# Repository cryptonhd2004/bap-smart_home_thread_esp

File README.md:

# Prvky chytré domácnosti s ESP32 používající protokol Thread

*Smart home components based on ESP32 using the Thread protocol*

Bakalářská práce, VUT v Brně, FEKT, Ústav telekomunikací, 2026/2027.

- **Autor:** David Šindelář
- **Vedoucí:** doc. Ing. Ivo Lattenberg, Ph.D.
- **Detail práce:** https://www.vut.cz/studenti/zav-prace/detail/179908

## Výkresy DPS a schémata

| Zařízení | Schéma zapojení | Osazovací výkres DPS | Další |
|---|---|---|---|
| Čidlo teploty | [PDF](https://github.com/cryptonhd2004/bap-smart_home_thread_esp/blob/main/esp_thread/schema_zapojeni.pdf) | [PDF](https://github.com/cryptonhd2004/bap-smart_home_thread_esp/blob/main/esp_thread/plots/esp_thread__Assembly.pdf) | [projekt KiCad](https://github.com/cryptonhd2004/bap-smart_home_thread_esp/tree/main/esp_thread) |
| Chytré světlo | [PDF](https://github.com/cryptonhd2004/bap-smart_home_thread_esp/blob/main/chytre_svetlo/schema_zapojeni.pdf) | [PDF](https://github.com/cryptonhd2004/bap-smart_home_thread_esp/blob/main/chytre_svetlo/plots/chytre_svetlo__Assembly.pdf) | [projekt KiCad](https://github.com/cryptonhd2004/bap-smart_home_thread_esp/tree/main/chytre_svetlo) |
| Bateriový vypínač | [PDF](https://github.com/cryptonhd2004/bap-smart_home_thread_esp/blob/main/Chytre_Tlacitko_BMS/schema_zapojeni.pdf) | [PDF](https://github.com/cryptonhd2004/bap-smart_home_thread_esp/blob/main/Chytre_Tlacitko_BMS/plots/Chytre_Tlacitko_BMS__Assembly.pdf) | [projekt KiCad](https://github.com/cryptonhd2004/bap-smart_home_thread_esp/tree/main/Chytre_Tlacitko_BMS) |

## O projektu

Návrh a realizace tří zařízení chytré domácnosti, která komunikují protokolem
Matter přes síť Thread (IEEE 802.15.4) a jsou integrována do Home Assistant:

| Zařízení | Napájení | Poznámka |
|---|---|---|
| Čidlo teploty | ze sítě | měření teploty, výběr čidla na základě porovnání |
| Chytré světlo | ze sítě | Router v síti Thread, RGB LED WS2812B (Matter light endpoint) |
| Bateriový vypínač | baterie | ošetření zákmitů, nízká spotřeba |

Všechna zařízení jsou postavena na čipu Espressif ESP32-C6
(modul Seeed Studio XIAO ESP32-C6).

## Struktura repozitáře

| Složka / soubor | Obsah |
|---|---|
| `bap_text/` | text práce (LaTeX, šablona VUT) |
| `chytre_svetlo/` | KiCad: chytré světlo (schéma, DPS, PDF schématu a osazení) |
| `Chytre_Tlacitko_BMS/` | KiCad: bateriový vypínač (schéma, DPS, PDF, iBOM) |
| `esp_thread/` | KiCad: chytrý teploměr (schéma, DPS, PDF, výrobní soubory v `production/`) |
| `test_builds/` | testovací firmware: `c6-matter-teplomer-firmware.factory.bin`, konfigurace `test-teplomer.yaml` a `tlacitko-thread.yaml` |
| `logs_for_debuging/` | logy z ladění, data a skripty porovnání čidel (`output/` – grafy) |
| `github_qr.*` | QR kód repozitáře pro osazení na DPS |

## Stav

| Část | Stav |
|---|---|
| Teoretický úvod (IEEE 802.15.4, CSA) | hotovo |
| Porovnání čidel teploty a vlhkosti | hotovo |
| Schéma a DPS – teploměr, světlo, vypínač | hotovo, připraveno k odsouhlasení |
| Firmware | testovací buildy (teploměr, tlačítko), RGB světlo rozpracováno |
| Text práce | rozpracováno (výsledky, návrh schémat) |

### Porovnání čidel

Referenční čidlo je SHT40 (jen klidné minuty). Rozdíl je počítán jako čidlo minus SHT40.

**Teplota** (n = 3292)

| Čidlo | střední rozdíl [°C] | s_d [°C] | RMSE [°C] | podíl \|d\| ≤ 0,7 °C |
|---|---|---|---|---|
| ALPSTUGA (SEN63C) | 0,19 | 0,18 | 0,26 | 100,0 % |
| BMP180 | −0,74 | 0,02 | 0,74 | 8,3 % |
| DHT11 | 0,00 | 0,04 | 0,04 | 100,0 % |
| TIMMERFLOTTE | −0,52 | 0,07 | 0,53 | 99,4 % |

**Vlhkost** (n = 2882)

| Čidlo | střední rozdíl [%RH] | s_d [%RH] | RMSE [%RH] | podíl \|d\| ≤ 3,0 %RH |
|---|---|---|---|---|
| ALPSTUGA (SEN63C) | −8,86 | 0,69 | 8,89 | 0,0 % |
| DHT11 | −1,70 | 0,94 | 1,94 | 99,9 % |
| TIMMERFLOTTE | −6,21 | 0,87 | 6,27 | 0,0 % |

## Sestavení textu

Hlavní soubor je `bap_text/sablona-prace.tex`. Překlad: pdfLaTeX dvakrát.
Seznam literatury je psán ručně v `bap_text/text/literatura.tex`.

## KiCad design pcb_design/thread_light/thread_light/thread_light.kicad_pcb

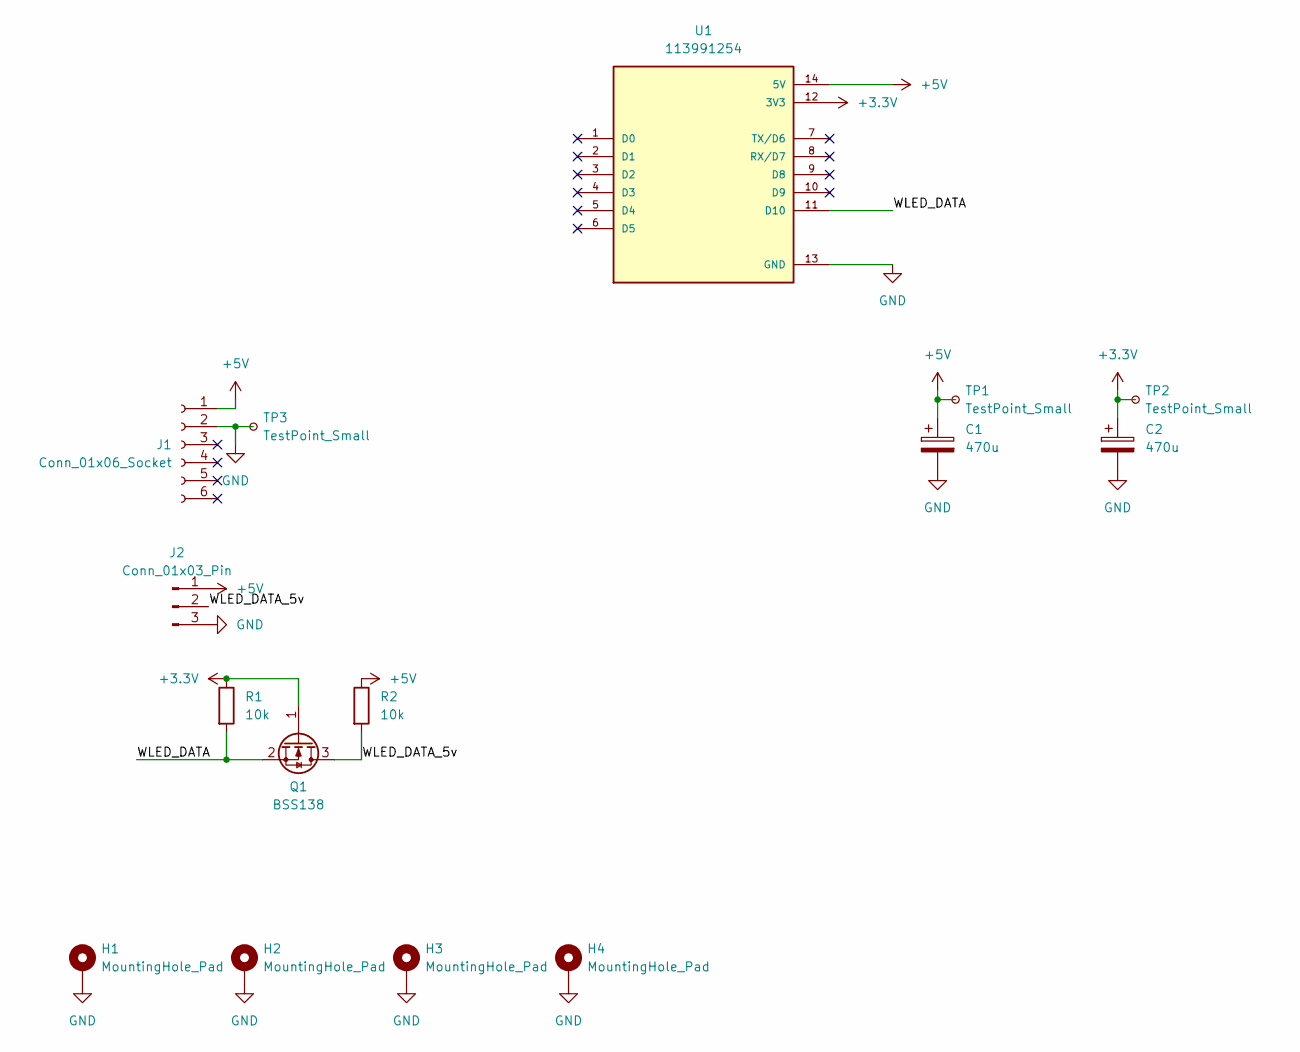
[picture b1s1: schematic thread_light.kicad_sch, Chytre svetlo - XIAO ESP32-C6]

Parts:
C1, C2: 470u; CP_Radial_D12.5mm_P5.00mm
H1, H2, H3, H4: MountingHole_Pad; MountingHole_3.2mm_M3_ISO14580_Pad_TopBottom
J1: Conn_01x06_Socket; PinSocket_1x06_P2.54mm_Vertical
J2: Conn_01x03_Pin; PinSocket_1x03_P2.54mm_Vertical
Q1: BSS138; SOT-23
R1, R2: 10k; R_0805_2012Metric
TP1, TP2, TP3: TestPoint_Small; TestPoint_Pad_D1.5mm
U1: 113991254; MODULE_113991254; PARTREV v1.0

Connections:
+3.3V: C2.1, Q1.1 (G), R1.1, TP2.1 (1_1), U1.12 (3V3)
+5V: C1.1, J1.1, J2.1, R2.1, TP1.1 (1_1), U1.14 (5V)
/WLED_DATA: Q1.2 (S), R1.2, U1.11 (D10)
/WLED_DATA_5v: J2.2, Q1.3 (D), R2.2
GND: C1.2, C2.2, H1.1 (1_1), H2.1 (1_1), H3.1 (1_1), H4.1 (1_1), J1.2, J2.3, TP3.1 (1_1), U1.13 (GND)

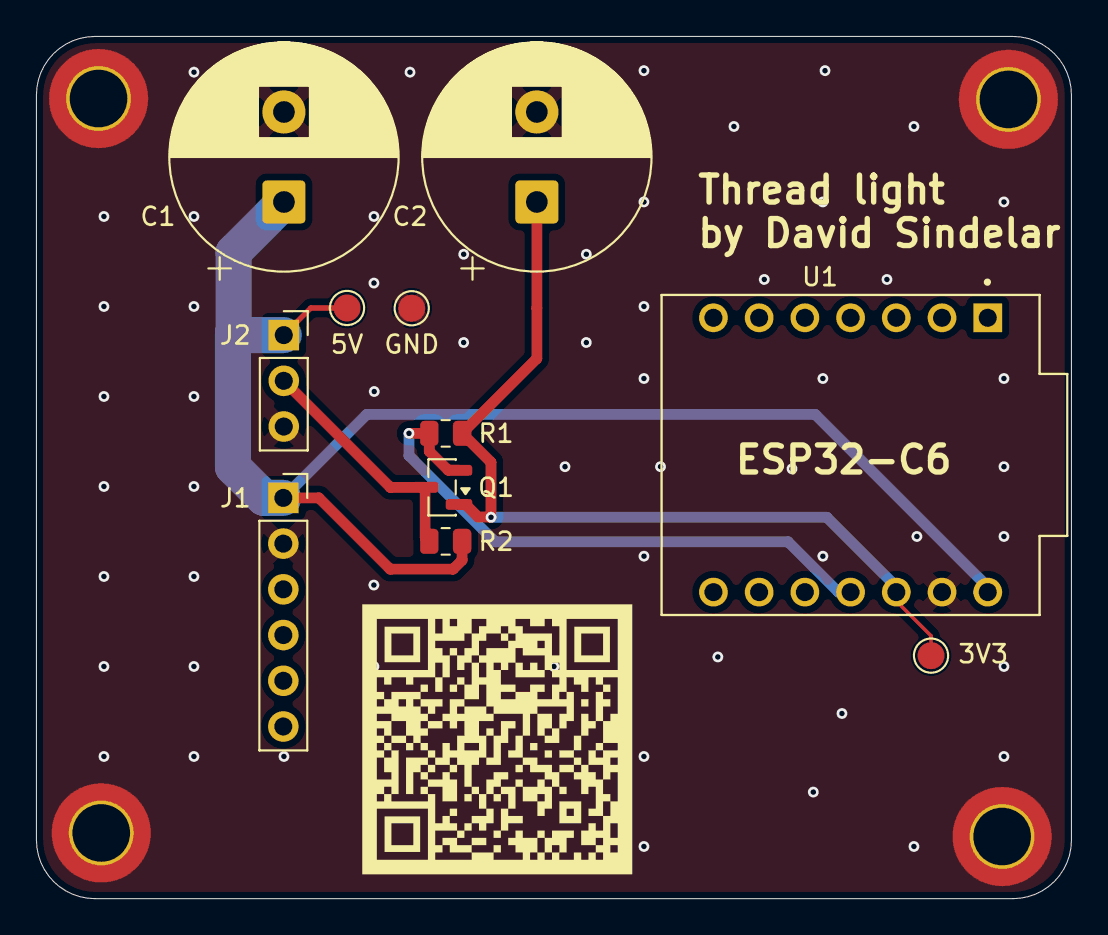
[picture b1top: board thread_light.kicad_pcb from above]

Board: 2 copper layers, 57.5 x 47.9 mm, 15 parts (0 on the bottom side), 5 nets.

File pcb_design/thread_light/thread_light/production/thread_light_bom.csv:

Designator,Footprint,Quantity,Value,LCSC Part #
"C1, C2",CP_Radial_D12.5mm_P5.00mm,2,470u,
J1,PinSocket_1x06_P2.54mm_Vertical,1,Conn_01x06_Socket,
J2,PinSocket_1x03_P2.54mm_Vertical,1,Conn_01x03_Pin,
Q1,SOT-23,1,BSS138,
"R1, R2",0805,2,10k,
"TP1, TP2, TP3",TestPoint_Pad_D1.5mm,3,TestPoint_Small,
U1,MODULE_113991254,1,113991254,

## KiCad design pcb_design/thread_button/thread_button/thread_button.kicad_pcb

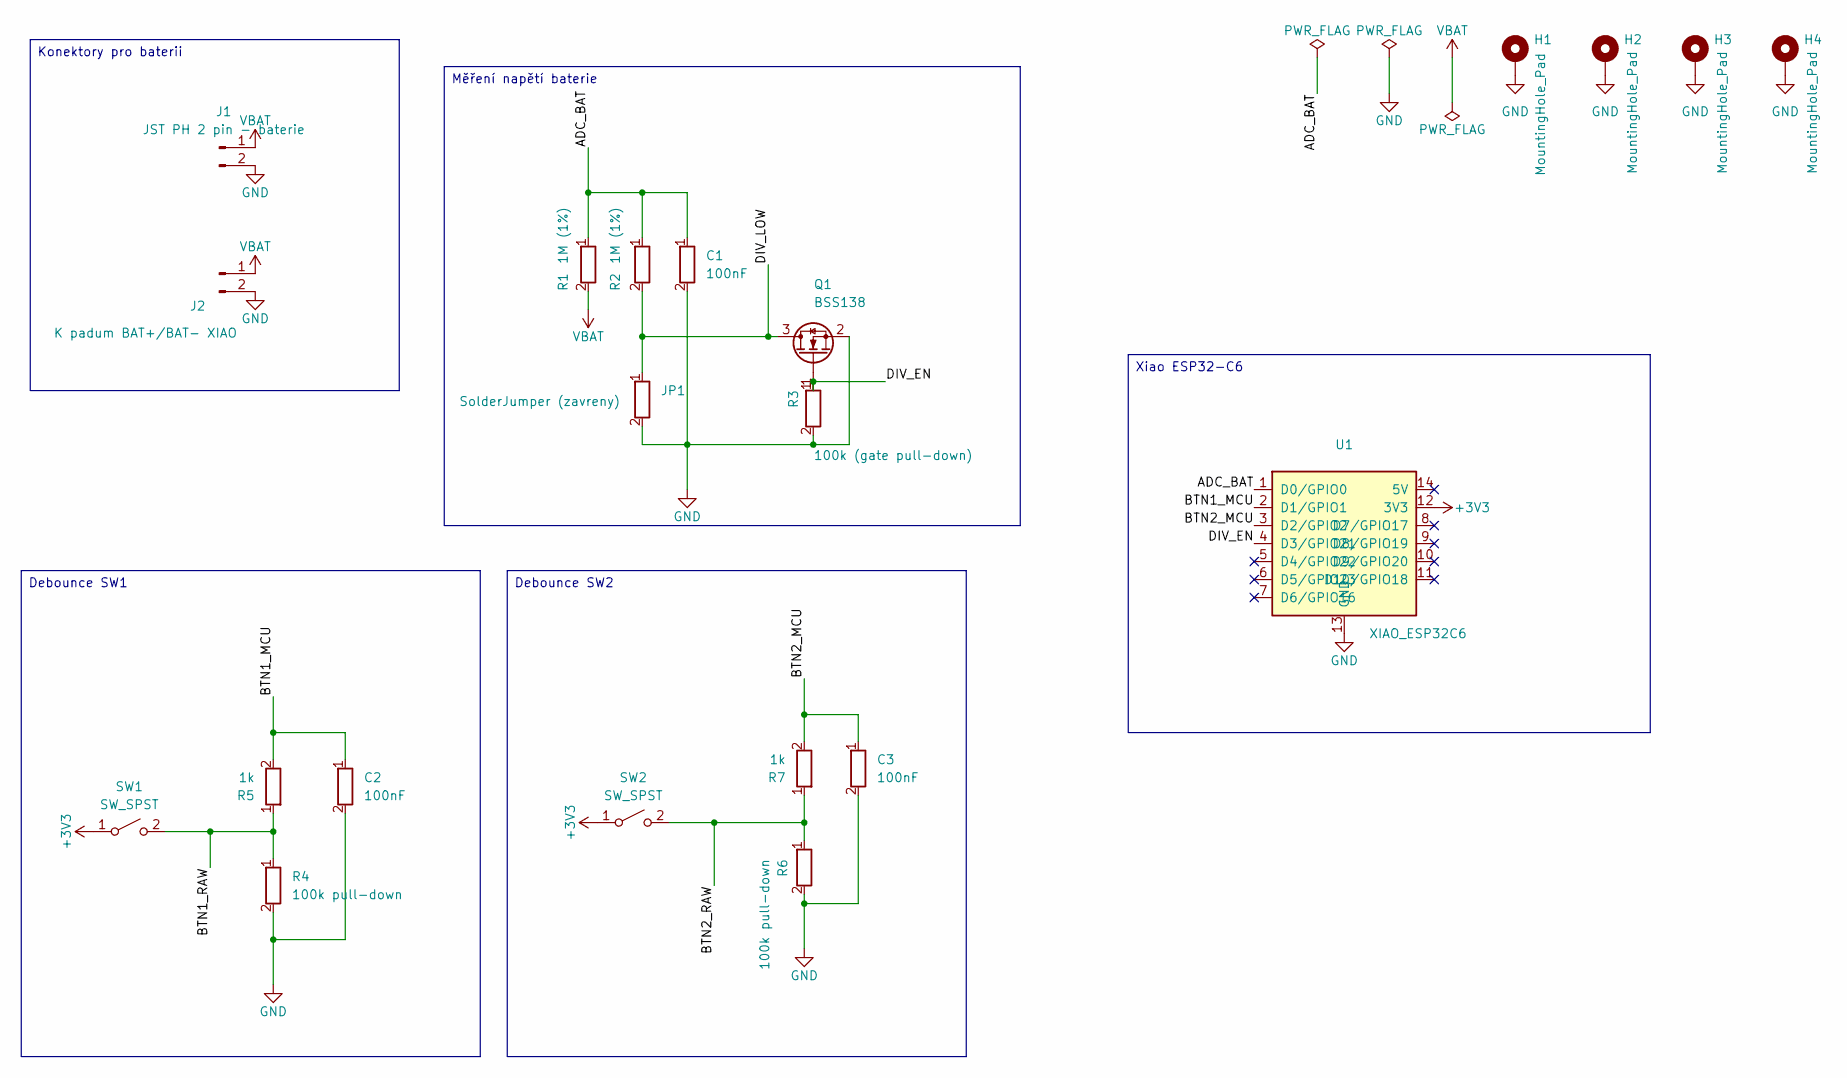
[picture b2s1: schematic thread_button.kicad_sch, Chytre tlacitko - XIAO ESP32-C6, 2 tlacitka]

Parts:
C1, C2, C3: 100nF; C_0805_2012Metric
H1, H2, H3, H4: MountingHole_Pad; MountingHole_2.5mm_Pad
J1: JST PH 2 pin - baterie; JST_PH_B2B-PH-K_1x02_P2.00mm_Vertical
J2: K padum BAT+/BAT- XIAO; JST_PH_B2B-PH-K_1x02_P2.00mm_Vertical
JP1: SolderJumper (zavreny); SolderJumper-2_P1.3mm_Bridged_RoundedPad1.0x1.5mm
Q1: BSS138; SOT-23
R1, R2: 1M (1%); R_0805_2012Metric
R3: 100k (gate pull-down); R_0805_2012Metric
R4, R6: 100k pull-down; R_0805_2012Metric
R5, R7: 1k; R_0805_2012Metric
SW1, SW2: SW_SPST; SW_PUSH-12mm_Wuerth-430476085716
U1: XIAO_ESP32C6; MODULE_113991254

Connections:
+3V3: SW1.1 (A), SW2.1 (A), U1.12 (3V3)
/ADC_BAT: C1.1, R1.1, R2.1, U1.1 (D0/GPIO0)
/BTN1_MCU: C2.1, R5.2, U1.2 (D1/GPIO1)
/BTN1_RAW: R4.1, R5.1, SW1.2 (B)
/BTN2_MCU: C3.1, R7.2, U1.3 (D2/GPIO2)
/BTN2_RAW: R6.1, R7.1, SW2.2 (B)
/DIV_EN: Q1.1 (G), R3.1, U1.4 (D3/GPIO21)
/DIV_LOW: JP1.1, Q1.3 (D), R2.2
GND: C1.2, C2.2, C3.2, H1.1 (1_1), H2.1 (1_1), H3.1 (1_1), H4.1 (1_1), J1.2, J2.2, JP1.2, Q1.2 (S), R3.2, R4.2, R6.2, U1.13 (GND)
VBAT: J1.1, J2.1, R1.2

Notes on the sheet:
Xiao ESP32-C6
Debounce SW2
Měření napětí baterie
Konektory pro baterii
Debounce SW1

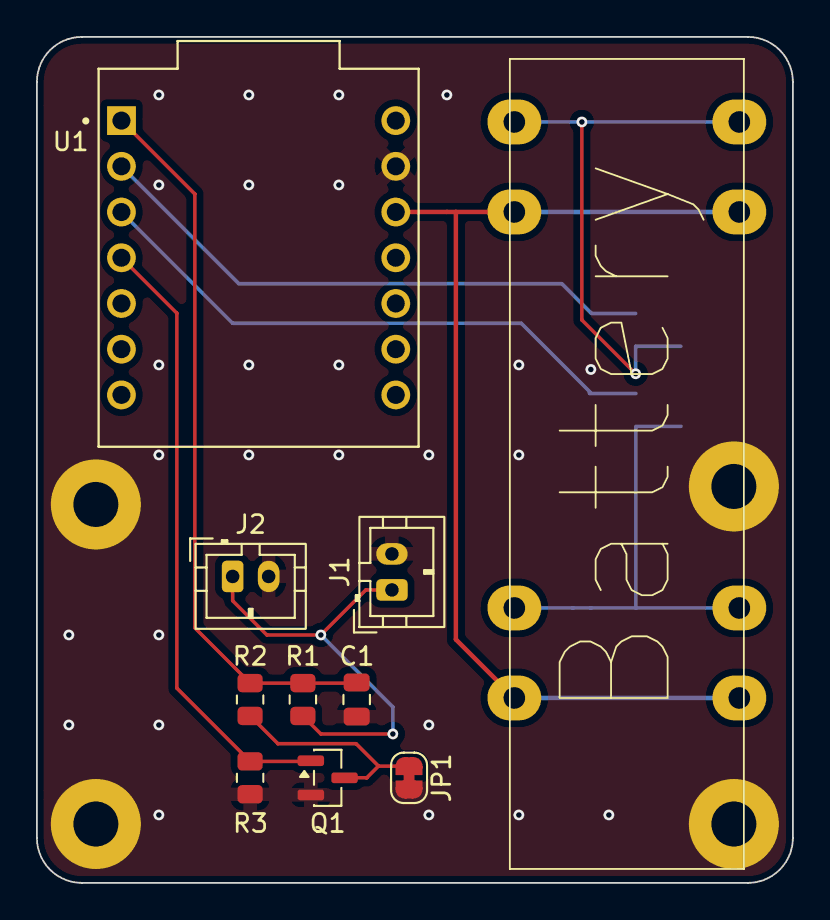
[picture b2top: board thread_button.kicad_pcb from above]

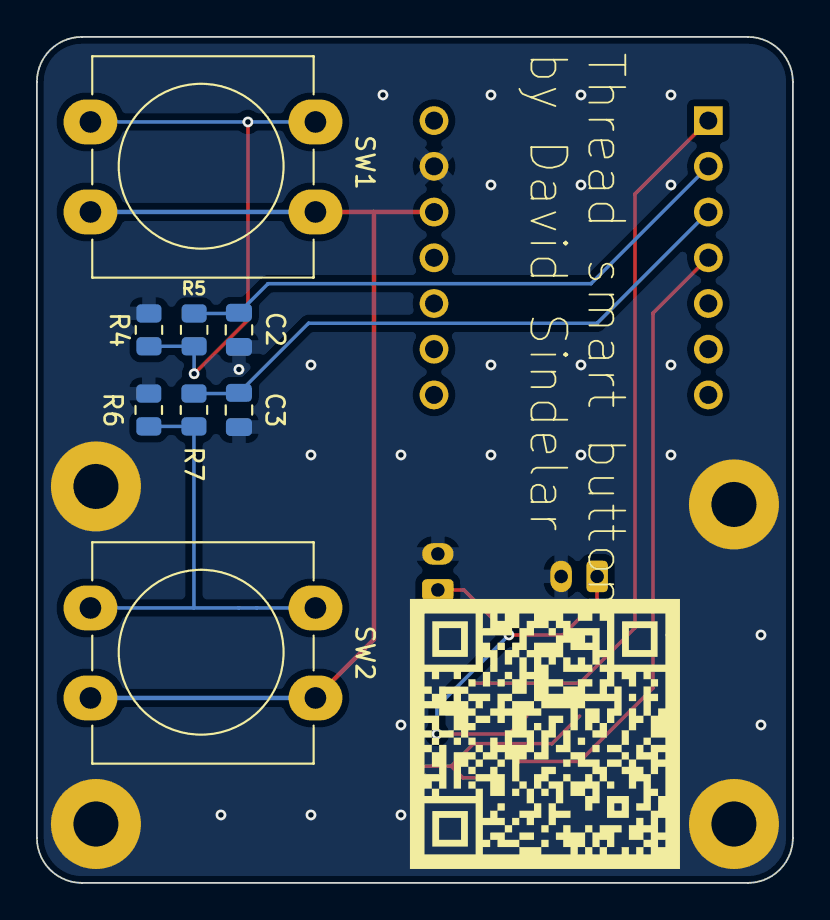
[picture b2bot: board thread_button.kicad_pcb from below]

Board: 2 copper layers, 42.0 x 47.0 mm, 21 parts (8 on the bottom side), 10 nets.

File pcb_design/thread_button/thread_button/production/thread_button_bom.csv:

Designator,Footprint,Quantity,Value,LCSC Part #
"C1, C2, C3",0805,3,100nF,
J1,JST_PH_B2B-PH-K_1x02_P2.00mm_Vertical,1,JST PH 2 pin - baterie,
J2,JST_PH_B2B-PH-K_1x02_P2.00mm_Vertical,1,K padum BAT+/BAT- XIAO,
JP1,SolderJumper-2_P1.3mm_Bridged_RoundedPad1.0x1.5mm,1,SolderJumper (zavreny),
Q1,SOT-23,1,BSS138,
"R1, R2",0805,2,1M (1%),
R3,0805,1,100k (gate pull-down),
"R4, R6",0805,2,100k pull-down,
"R5, R7",0805,2,1k,
"SW1, SW2",SW_PUSH-12mm_Wuerth-430476085716,2,SW_SPST,
U1,MODULE_113991254,1,XIAO_ESP32C6,

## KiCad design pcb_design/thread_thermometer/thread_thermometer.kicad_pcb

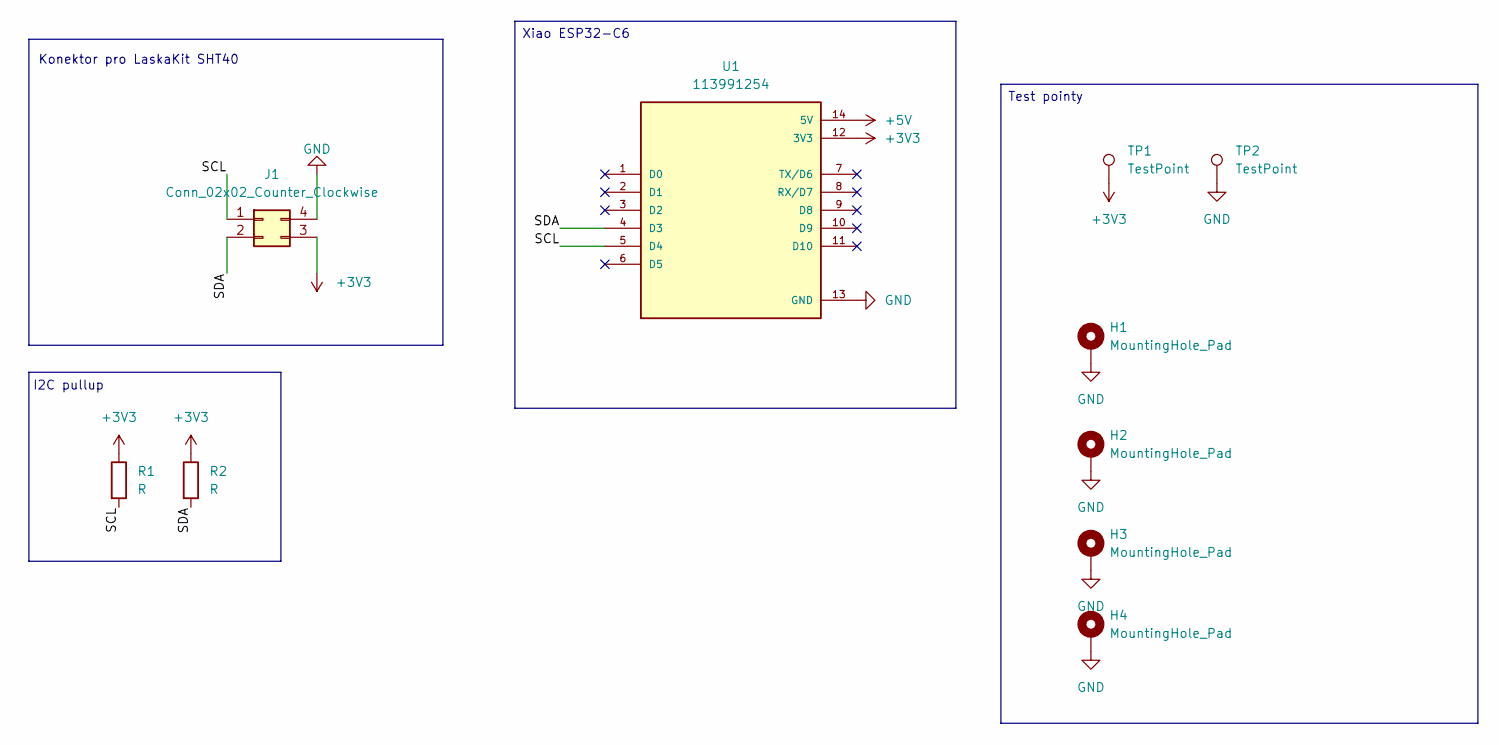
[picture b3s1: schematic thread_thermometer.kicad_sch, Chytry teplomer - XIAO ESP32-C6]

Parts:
H1, H2, H3, H4: MountingHole_Pad; MountingHole_2.5mm_Pad
J1: Conn_02x02_Counter_Clockwise; PinSocket_2x02_P2.54mm_Vertical
R1, R2: R; R_0805_2012Metric
TP1, TP2: TestPoint; TestPoint_Pad_D1.5mm
U1: 113991254; MODULE_113991254; PARTREV v1.0

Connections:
+3V3: J1.3, R1.1, R2.1, TP1.1 (1_1), U1.12 (3V3)
+5V: U1.14 (5V)
/SCL: J1.1, R1.2, U1.5 (D4)
/SDA: J1.2, R2.2, U1.4 (D3)
GND: H1.1 (1_1), H2.1 (1_1), H3.1 (1_1), H4.1 (1_1), J1.4, TP2.1 (1_1), U1.13 (GND)

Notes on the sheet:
Konektor pro LaskaKit SHT40
I2C pullup
Test pointy
Xiao ESP32-C6

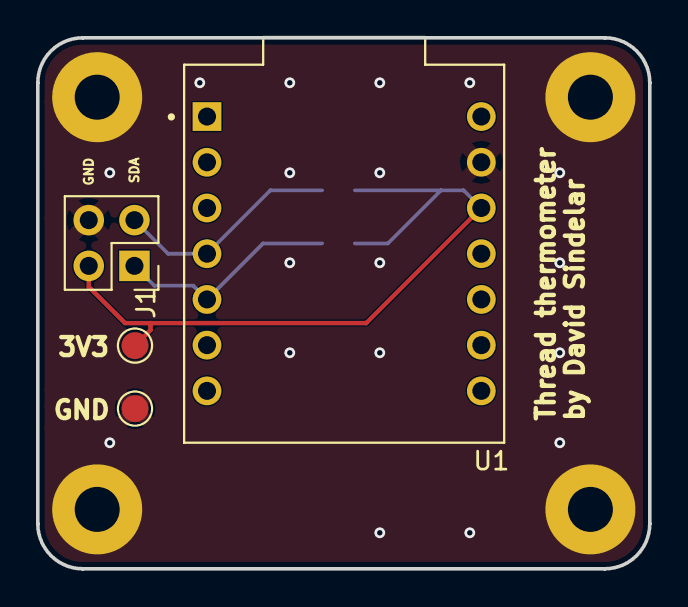
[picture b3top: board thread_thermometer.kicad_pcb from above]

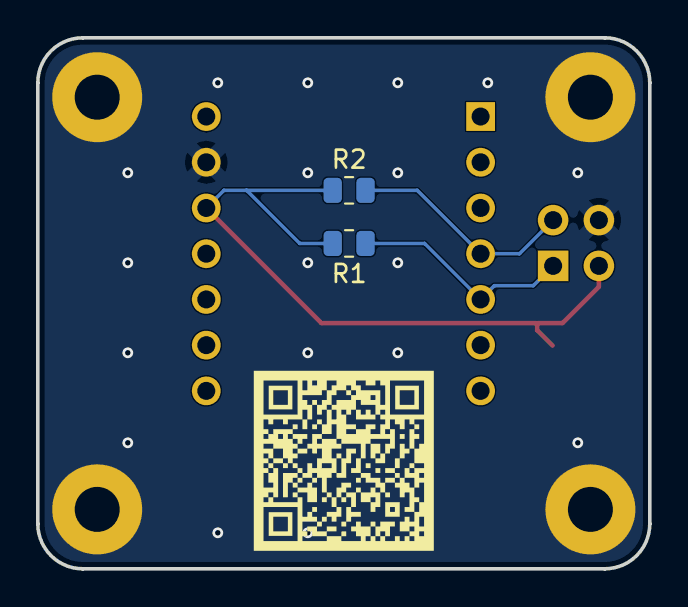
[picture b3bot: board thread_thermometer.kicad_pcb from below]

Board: 2 copper layers, 34.0 x 29.5 mm, 10 parts (2 on the bottom side), 4 nets.

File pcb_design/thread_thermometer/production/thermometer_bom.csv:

Designator,Footprint,Quantity,Value,LCSC Part #
J1,PinSocket_2x02_P2.54mm_Vertical,1,Conn_02x02_Counter_Clockwise,
"R1, R2",0805,2,R,
"TP1, TP2",TestPoint_Pad_D1.5mm,2,TestPoint,
U1,MODULE_113991254,1,113991254,
